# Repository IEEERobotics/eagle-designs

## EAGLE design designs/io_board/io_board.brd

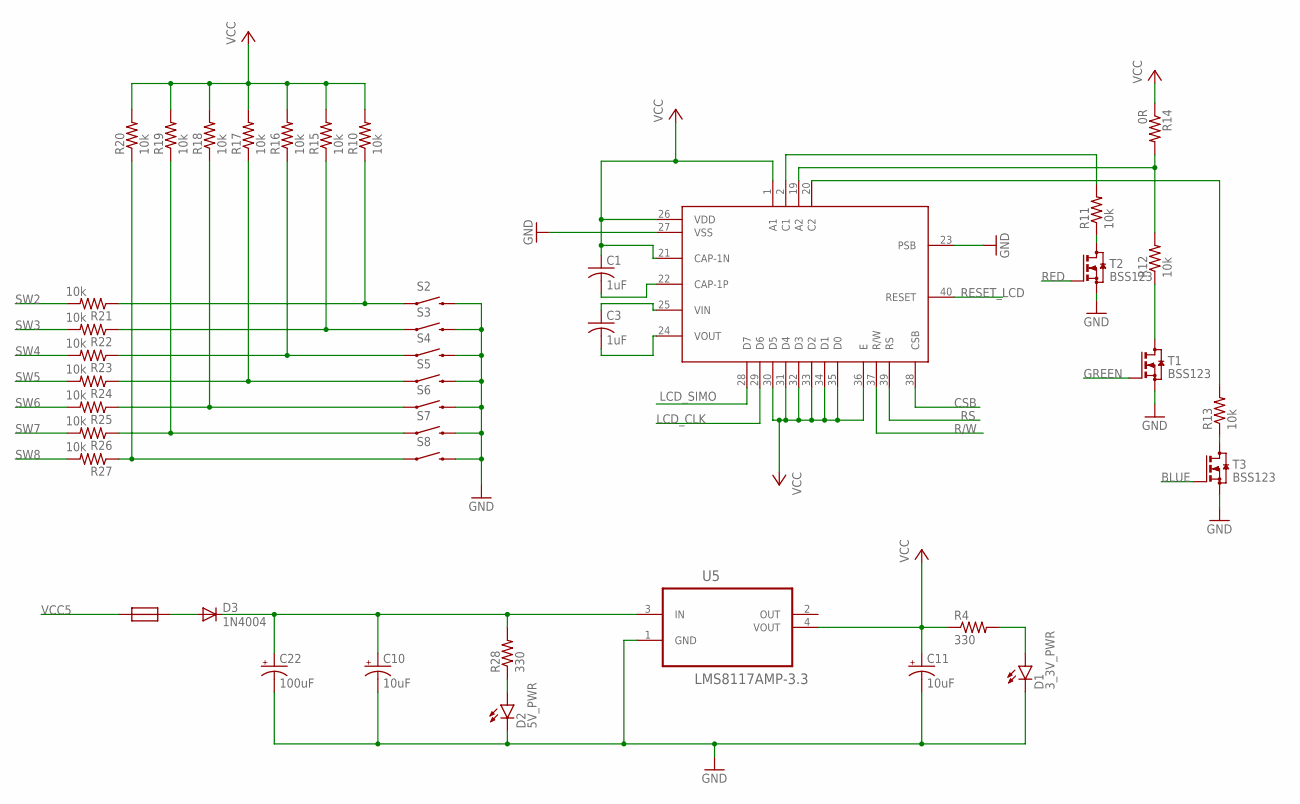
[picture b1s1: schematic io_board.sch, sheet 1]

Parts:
C1, C3: 1uF; C1206K
C10, C11: 10uF; EIA3216
C22: 100uF; EIA7343
D1: 3_3V_PWR; FKIT-LED-1206
D2: 5V_PWR; FKIT-LED-1206
D3: 1N4004; DO41-10
R4, R28: 330; R0805W
R10, R11, R12, R13, R15, R16, R17, R18, R19, R20, R21, R22, R23, R24, R25, R26, R27: 10k; R1206W
R14: 0R; R1206W
S2, S3, S4, S5, S6, S7, S8: SWITCH-MOMENTARY-2SMD-4; TACTILE_SWITCH_TALL
T1, T2, T3: BSS123; SOT23
U5: LMS8117AMP-3.3; SOT230P696X180-4N
U$2: EA_DOGMXXX-A; EADOGM
U$3: NANO_FUSE

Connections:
BLUE: T3.1 (G); also elsewhere on the board
CSB: U$2.38 (CSB); also elsewhere on the board
GND: C10.C (-), C11.C (-), C22.C (-), D1.C, D2.C, S2.B2 (2), S3.B2 (2), S4.B2 (2), S5.B2 (2), S6.B2 (2), S7.B2 (2), S8.B2 (2), T1.2 (S), T2.2 (S), T3.2 (S), U5.1 (GND), U$2.23 (PSB), U$2.27 (VSS); also elsewhere on the board
GREEN: T1.1 (G); also elsewhere on the board
LCD_CLK: U$2.29 (D6); also elsewhere on the board
LCD_SIMO: U$2.28 (D7); also elsewhere on the board
unnamed: R12.2, R14.2, U$2.19 (A2)
unnamed: R11.1, T2.3 (D)
unnamed: R12.1, T1.3 (D)
unnamed: R13.1, T3.3 (D)
unnamed: R11.2, U$2.2 (C1)
unnamed: R13.2, U$2.20 (C2)
unnamed: C1.2, U$2.22 (CAP-1P)
unnamed: C3.1, U$2.25 (VIN)
unnamed: C3.2, U$2.24 (VOUT)
unnamed: R10.1, R21.1, S2.A2 (1)
unnamed: R15.1, R22.1, S3.A2 (1)
unnamed: R16.1, R23.1, S4.A2 (1)
unnamed: R17.1, R24.1, S5.A2 (1)
unnamed: R18.1, R25.1, S6.A2 (1)
unnamed: R19.1, R26.1, S7.A2 (1)
unnamed: R20.1, R27.1, S8.A2 (1)
unnamed: D1.A, R4.2
unnamed: D2.A, R28.1
unnamed: D3.A, U$3.2
unnamed: C10.A (+), C22.A (+), D3.C, R28.2, U5.3 (IN)
R/W: U$2.37 (R/W); also elsewhere on the board
RED: T2.1 (G); also elsewhere on the board
RESET_LCD: U$2.40 (RESET); also elsewhere on the board
RS: U$2.39 (RS)
SW2: R21.2; also elsewhere on the board
SW3: R22.2; also elsewhere on the board
SW4: R23.2; also elsewhere on the board
SW5: R24.2; also elsewhere on the board
SW6: R25.2; also elsewhere on the board
SW7: R26.2; also elsewhere on the board
SW8: R27.2; also elsewhere on the board
VCC: C1.1, C11.A (+), R4.1, R10.2, R14.1, R15.2, R16.2, R17.2, R18.2, R19.2, R20.2, U5.4 (VOUT), U$2.1 (A1), U$2.21 (CAP-1N), U$2.26 (VDD), U$2.30 (D5), U$2.31 (D4), U$2.32 (D3), U$2.33 (D2), U$2.34 (D1), U$2.35 (D0), U$2.36 (E); also elsewhere on the board
VCC5: U$3.1; also elsewhere on the board

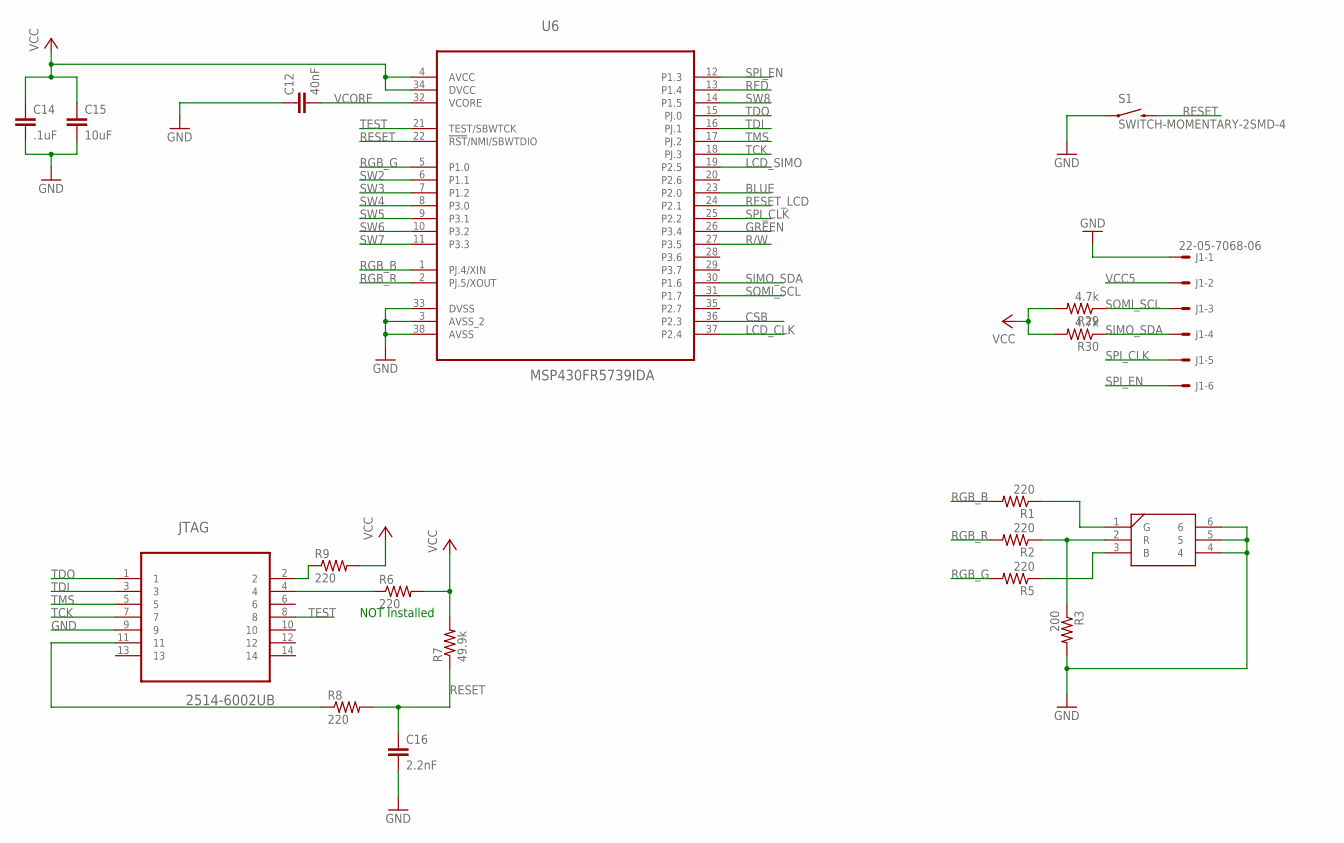
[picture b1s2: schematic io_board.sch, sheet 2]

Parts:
C12: 40nF; 0805
C14: .1uF; 0805
C15: 10uF; 0805
C16: 2.2nF; 0805
J1: 22-05-7068-06; 7395-06
JTAG: 2514-6002UB; 3M_2514-6002UB
R1, R2, R5, R6, R8, R9: 220; R0805W
R3: 200; R0805W
R7: 49.9k; R0805W
R29, R30: 4.7k; R0805W
S1: SWITCH-MOMENTARY-2SMD-4; TACTILE_SWITCH_TALL
U6: MSP430FR5739IDA; SOP65P810X120-38N
U$7: RGB; RGB_SMD

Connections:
BLUE: U6.23 (P2.0); also elsewhere on the board
CSB: U6.36 (P2.3); also elsewhere on the board
GND: C12.1, C14.2, C15.2, C16.2, J1.1, JTAG.9, R3.2, S1.A2 (1), U6.3 (AVSS_2), U6.33 (DVSS), U6.38 (AVSS), U$7.4, U$7.5, U$7.6; also elsewhere on the board
GREEN: U6.26 (P3.4); also elsewhere on the board
LCD_CLK: U6.37 (P2.4); also elsewhere on the board
LCD_SIMO: U6.19 (P2.5); also elsewhere on the board
unnamed: JTAG.4, R6.1
unnamed: JTAG.2, R9.1
unnamed: R2.1, R3.1, U$7.2 (R)
unnamed: JTAG.11, R8.1
unnamed: R5.1, U$7.3 (B)
unnamed: R1.1, U$7.1 (G)
R/W: U6.27 (P3.5); also elsewhere on the board
RED: U6.13 (P1.4); also elsewhere on the board
RESET: C16.1, R7.1, R8.2, S1.B2 (2), U6.22 (!RST!/NMI/SBWTDIO)
RESET_LCD: U6.24 (P2.1); also elsewhere on the board
RGB_B: R1.2, U6.1 (PJ.4/XIN)
RGB_G: R5.2, U6.5 (P1.0)
RGB_R: R2.2, U6.2 (PJ.5/XOUT)
SIMO_SDA: J1.4, R30.1, U6.30 (P1.6)
SOMI_SCL: J1.3, R29.1, U6.31 (P1.7)
SPI_CLK: J1.5, U6.25 (P2.2)
SPI_EN: J1.6, U6.12 (P1.3)
SW2: U6.6 (P1.1); also elsewhere on the board
SW3: U6.7 (P1.2); also elsewhere on the board
SW4: U6.8 (P3.0); also elsewhere on the board
SW5: U6.9 (P3.1); also elsewhere on the board
SW6: U6.10 (P3.2); also elsewhere on the board
SW7: U6.11 (P3.3); also elsewhere on the board
SW8: U6.14 (P1.5); also elsewhere on the board
TCK: JTAG.7, U6.18 (PJ.3)
TDI: JTAG.3, U6.16 (PJ.1)
TDO: JTAG.1, U6.15 (PJ.0)
TEST: JTAG.8, U6.21 (TEST/SBWTCK)
TMS: JTAG.5, U6.17 (PJ.2)
VCC: C14.1, C15.1, R6.2, R7.2, R9.2, R29.2, R30.2, U6.4 (AVCC), U6.34 (DVCC); also elsewhere on the board
VCC5: J1.2; also elsewhere on the board
VCORE: C12.2, U6.32 (VCORE)

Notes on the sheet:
NOT Installed

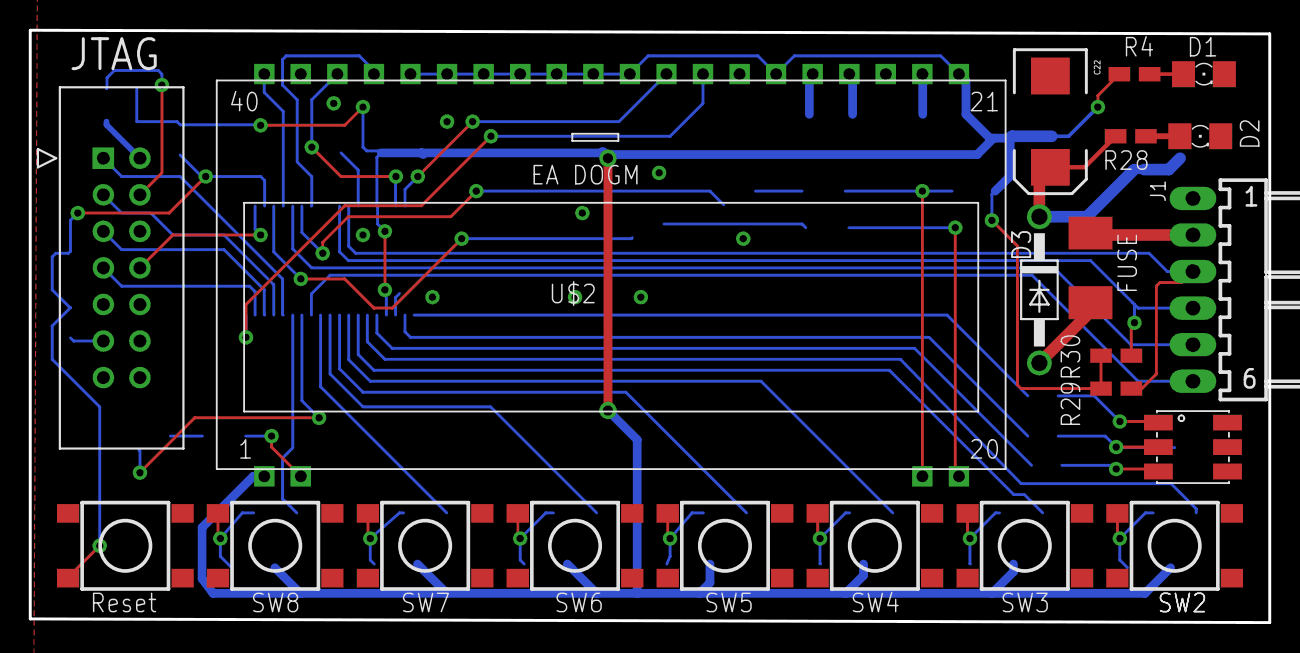
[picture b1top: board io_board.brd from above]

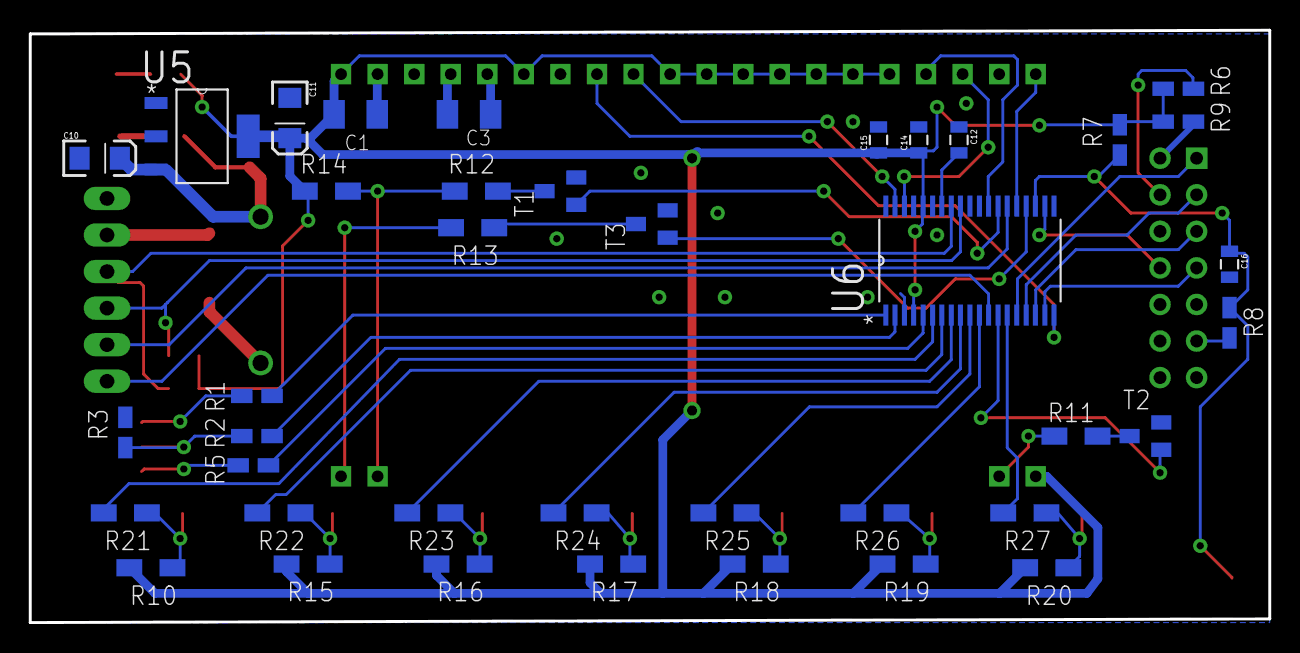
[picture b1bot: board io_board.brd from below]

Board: 2 copper layers, 86.1 x 41.1 mm, 60 parts (39 on the bottom side), 58 nets.

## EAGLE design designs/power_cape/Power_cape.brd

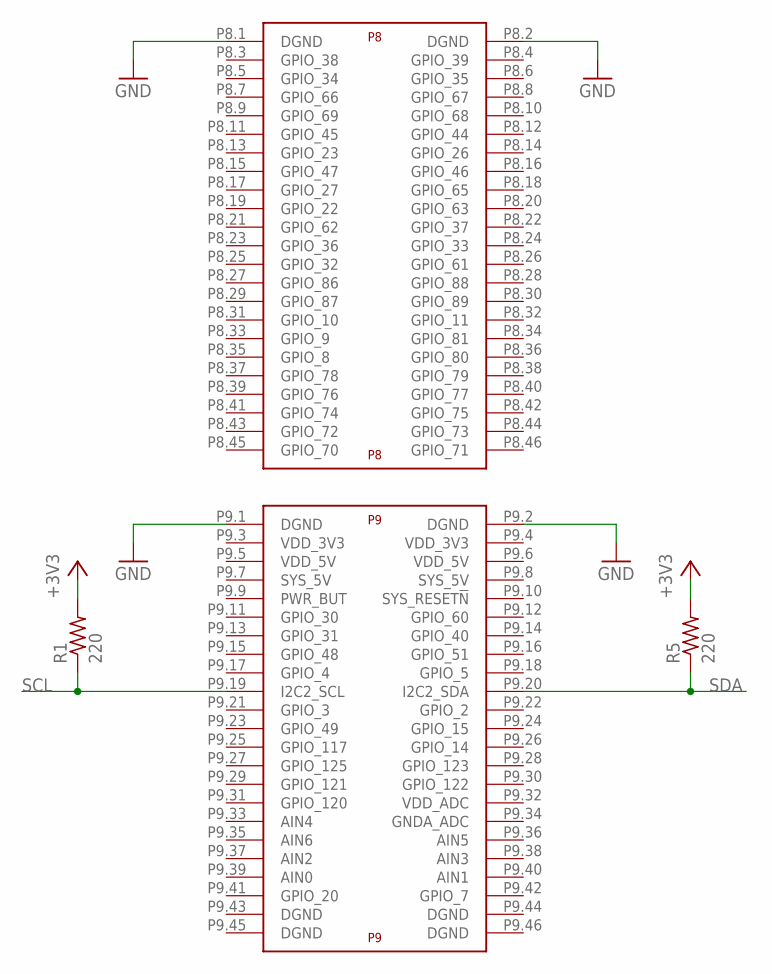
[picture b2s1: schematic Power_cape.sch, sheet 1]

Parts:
R1, R5: 220; R0805W
U$1: BEAGLE_BONE_BLACK_CAPE

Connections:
+3V3: R1.2, R5.2
GND: U$1.P8.1 (DGND), U$1.P8.2 (DGND), U$1.P9.1 (DGND), U$1.P9.2 (DGND); also elsewhere on the board
SCL: R1.1, U$1.P9.19 (I2C2_SCL)
SDA: R5.1, U$1.P9.20 (I2C2_SDA)

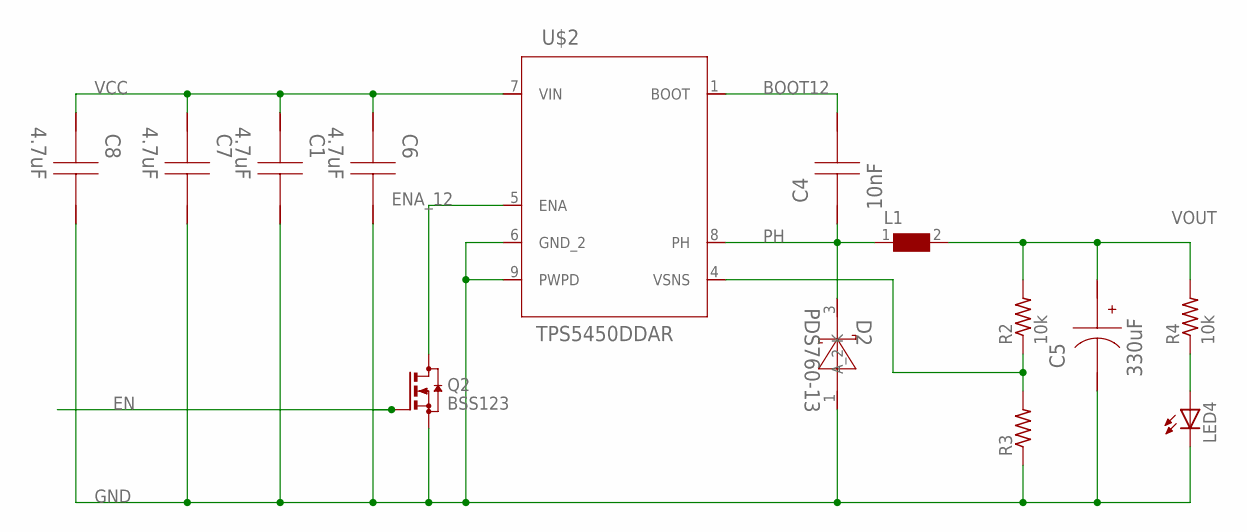
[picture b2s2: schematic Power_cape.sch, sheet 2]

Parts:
C1, C6, C7, C8: 4.7uF; 1206
C4: 10nF; 0805
C5: 330uF; SM_RADIAL_10AMM
D2: PDS760-13; POWERDI5
L1: WE-HCC-7443331000_1090; WE-HCC_1090
LED4: LEDSML1206; SML1206
Q2: BSS123; SOT23
R2, R4: 10k; R1206
R3: R-US_R1206; R1206
U$2: TPS5450DDAR; R-PDSO-G8

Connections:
BOOT12: C4.1, U$2.1 (BOOT)
EN: Q2.1 (G)
ENA_12: Q2.3 (D), U$2.5 (ENA)
GND: C1.1, C5.2 (-), C6.1, C7.1, C8.1, D2.1 (A_2), LED4.C, Q2.2 (S), R3.1, U$2.6 (GND_2), U$2.9 (PWPD); also elsewhere on the board
unnamed: LED4.A, R4.1
PH: C4.2, D2.3 (K), L1.1, U$2.8 (PH)
VCC: C1.2, C6.2, C7.2, C8.2, U$2.7 (VIN)
VOUT: C5.1 (+), L1.2, R2.2, R4.2
VSNS12: R2.1, R3.2, U$2.4 (VSNS)

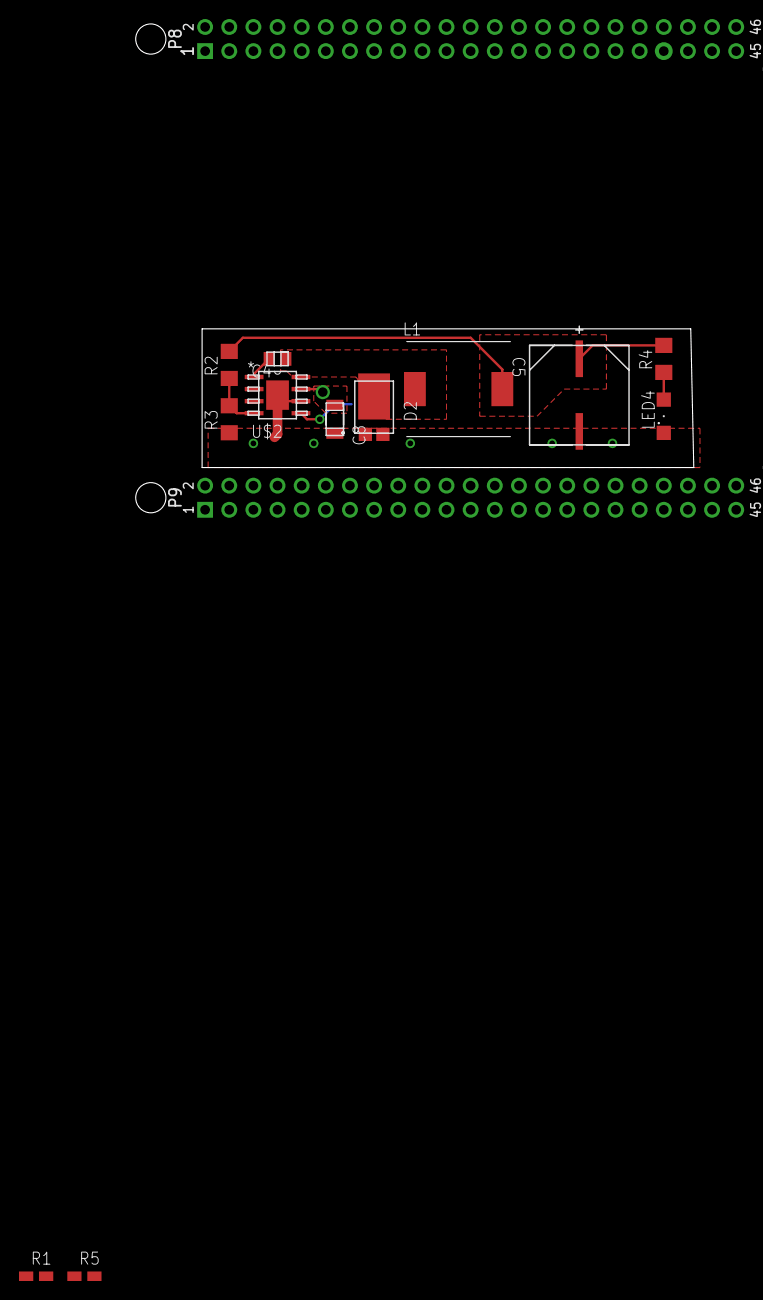
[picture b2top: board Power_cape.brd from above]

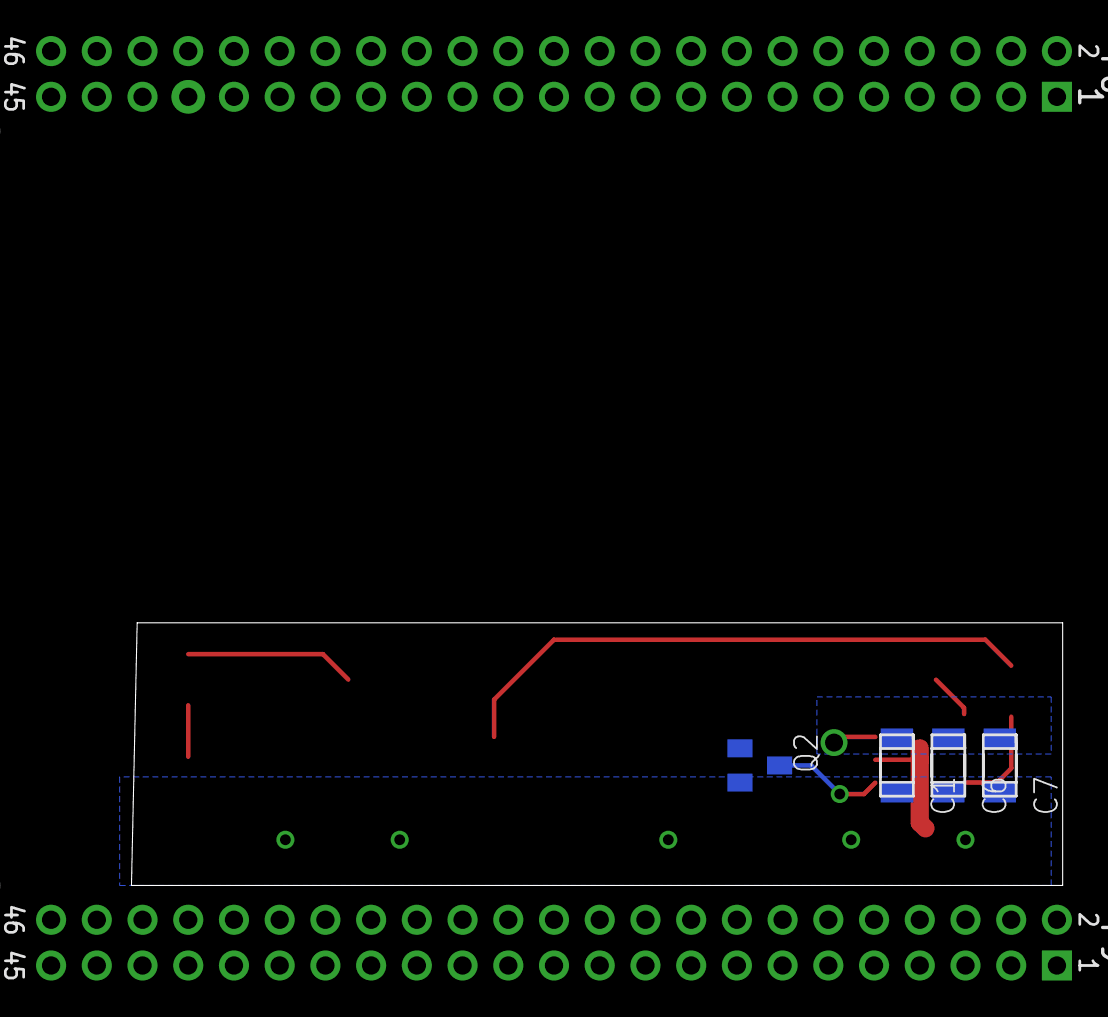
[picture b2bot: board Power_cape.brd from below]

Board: 2 copper layers, 51.7 x 14.6 mm, 17 parts (4 on the bottom side), 11 nets.

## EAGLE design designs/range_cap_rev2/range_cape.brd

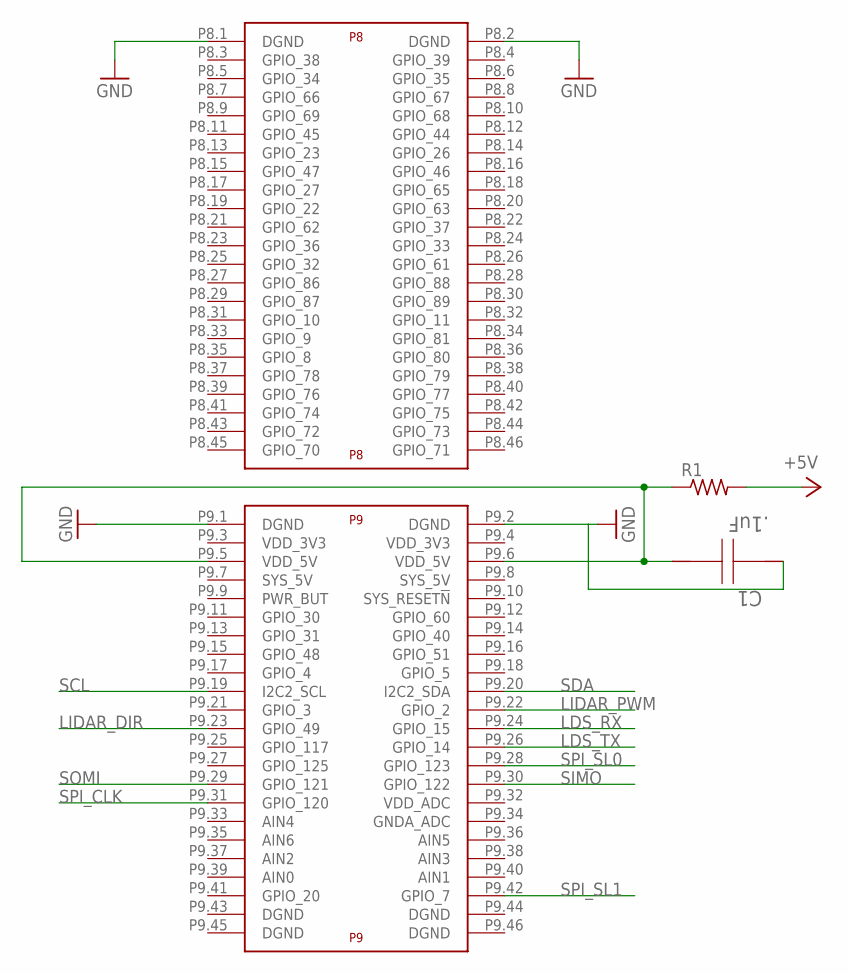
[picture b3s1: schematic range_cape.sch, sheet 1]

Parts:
C1: .1uF; 1206
R1: R-US_R1206; R1206
U$1: BEAGLE_BONE_BLACK_CAPE

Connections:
+5V: R1.2; also elsewhere on the board
GND: C1.2, U$1.P8.1 (DGND), U$1.P8.2 (DGND), U$1.P9.1 (DGND), U$1.P9.2 (DGND); also elsewhere on the board
LDS_RX: U$1.P9.24 (GPIO_15); also elsewhere on the board
LDS_TX: U$1.P9.26 (GPIO_14); also elsewhere on the board
LIDAR_DIR: U$1.P9.23 (GPIO_49); also elsewhere on the board
LIDAR_PWM: U$1.P9.22 (GPIO_2); also elsewhere on the board
unnamed: C1.1, R1.1, U$1.P9.5 (VDD_5V), U$1.P9.6 (VDD_5V)
SCL: U$1.P9.19 (I2C2_SCL); also elsewhere on the board
SDA: U$1.P9.20 (I2C2_SDA); also elsewhere on the board
SIMO: U$1.P9.30 (GPIO_122); also elsewhere on the board
SOMI: U$1.P9.29 (GPIO_121); also elsewhere on the board
SPI_CLK: U$1.P9.31 (GPIO_120); also elsewhere on the board
SPI_SL0: U$1.P9.28 (GPIO_123); also elsewhere on the board
SPI_SL1: U$1.P9.42 (GPIO_7); also elsewhere on the board

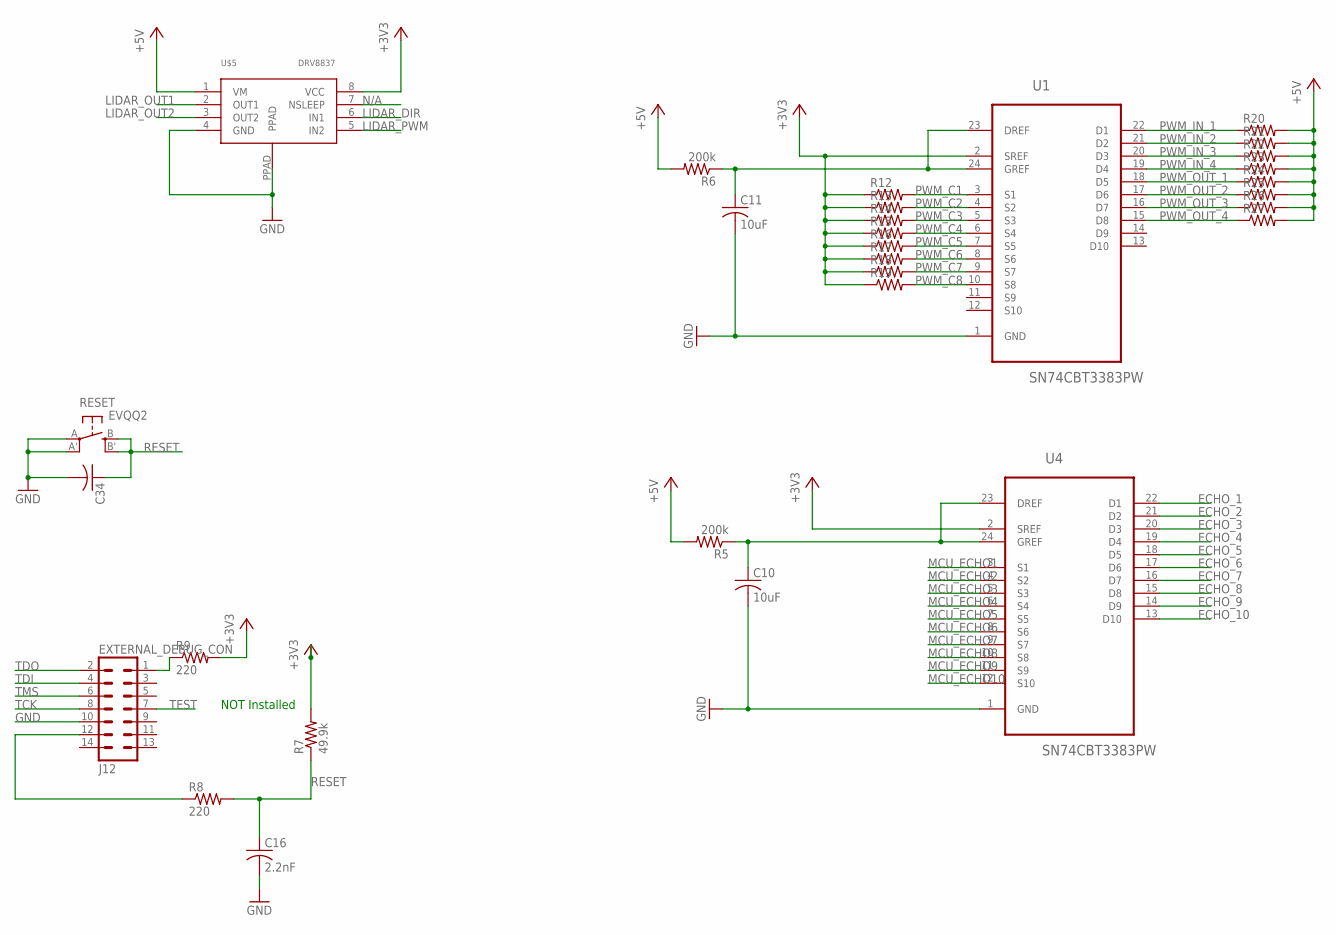
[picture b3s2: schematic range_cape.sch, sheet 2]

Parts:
C10, C11: 10uF; C0805
C16: 2.2nF; C0603
C34: C-USC1206; C1206
J12: EXTERNAL_DEBUG_CON; EXTERNAL_DEBUG
R5, R6: 200k; R0603
R7: 49.9k; R0603
R8, R9: 220; R0603
R12, R13, R14, R15, R16, R17, R18, R19, R20, R21, R22, R23, R24, R25, R26, R27: R-US_R0402; R0402
RESET: EVQQ2; EVQ-Q2
U1, U4: SN74CBT3383PW; SOP65P640X120-24N
U$5: DRV8837; WSON-8

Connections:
+3V3: R7.2, R9.2, R12.1, R13.1, R14.1, R15.1, R16.1, R17.1, R18.1, R19.1, U1.2 (SREF), U4.2 (SREF), U$5.8 (VCC); also elsewhere on the board
+5V: R5.2, R6.2, R20.2, R21.2, R22.2, R23.2, R24.2, R25.2, R26.2, R27.2, U$5.1 (VM); also elsewhere on the board
ECHO_1: U4.22 (D1); also elsewhere on the board
ECHO_2: U4.21 (D2); also elsewhere on the board
ECHO_3: U4.20 (D3); also elsewhere on the board
ECHO_4: U4.19 (D4); also elsewhere on the board
ECHO_5: U4.18 (D5); also elsewhere on the board
ECHO_6: U4.17 (D6); also elsewhere on the board
ECHO_7: U4.16 (D7); also elsewhere on the board
ECHO_8: U4.15 (D8); also elsewhere on the board
ECHO_9: U4.14 (D9); also elsewhere on the board
ECHO_10: U4.13 (D10); also elsewhere on the board
GND: C10.2, C11.2, C16.2, C34.2, J12.10, RESET.A, RESET.A' (P1), U1.1 (GND), U4.1 (GND), U$5.4 (GND), U$5.PPAD; also elsewhere on the board
LIDAR_DIR: U$5.6 (IN1); also elsewhere on the board
LIDAR_OUT1: U$5.2 (OUT1); also elsewhere on the board
LIDAR_OUT2: U$5.3 (OUT2); also elsewhere on the board
LIDAR_PWM: U$5.5 (IN2); also elsewhere on the board
MCU_ECHO1: U4.3 (S1); also elsewhere on the board
MCU_ECHO2: U4.4 (S2); also elsewhere on the board
MCU_ECHO3: U4.5 (S3); also elsewhere on the board
MCU_ECHO4: U4.6 (S4); also elsewhere on the board
MCU_ECHO5: U4.7 (S5); also elsewhere on the board
MCU_ECHO6: U4.8 (S6); also elsewhere on the board
MCU_ECHO7: U4.9 (S7); also elsewhere on the board
MCU_ECHO8: U4.10 (S8); also elsewhere on the board
MCU_ECHO9: U4.11 (S9); also elsewhere on the board
MCU_ECHO10: U4.12 (S10); also elsewhere on the board
unnamed: C11.1, R6.1, U1.23 (DREF), U1.24 (GREF)
unnamed: J12.12, R8.1
unnamed: J12.1, R9.1
unnamed: C10.1, R5.1, U4.23 (DREF), U4.24 (GREF)
N/A: U$5.7 (NSLEEP)
PWM_C1: R12.2, U1.3 (S1); also elsewhere on the board
PWM_C2: R13.2, U1.4 (S2); also elsewhere on the board
PWM_C3: R14.2, U1.5 (S3); also elsewhere on the board
PWM_C4: R15.2, U1.6 (S4); also elsewhere on the board
PWM_C5: R16.2, U1.7 (S5); also elsewhere on the board
PWM_C6: R17.2, U1.8 (S6); also elsewhere on the board
PWM_C7: R18.2, U1.9 (S7); also elsewhere on the board
PWM_C8: R19.2, U1.10 (S8); also elsewhere on the board
PWM_IN_1: R20.1, U1.22 (D1); also elsewhere on the board
PWM_IN_2: R21.1, U1.21 (D2); also elsewhere on the board
PWM_IN_3: R22.1, U1.20 (D3); also elsewhere on the board
PWM_IN_4: R23.1, U1.19 (D4); also elsewhere on the board
PWM_OUT_1: R24.1, U1.18 (D5); also elsewhere on the board
PWM_OUT_2: R25.1, U1.17 (D6); also elsewhere on the board
PWM_OUT_3: R26.1, U1.16 (D7); also elsewhere on the board
PWM_OUT_4: R27.1, U1.15 (D8); also elsewhere on the board
RESET: C16.1, C34.1, R7.1, R8.2, RESET.B (S), RESET.B' (S1); also elsewhere on the board
TCK: J12.8; also elsewhere on the board
TDI: J12.4; also elsewhere on the board
TDO: J12.2; also elsewhere on the board
TEST: J12.7; also elsewhere on the board
TMS: J12.6; also elsewhere on the board

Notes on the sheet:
NOT Installed

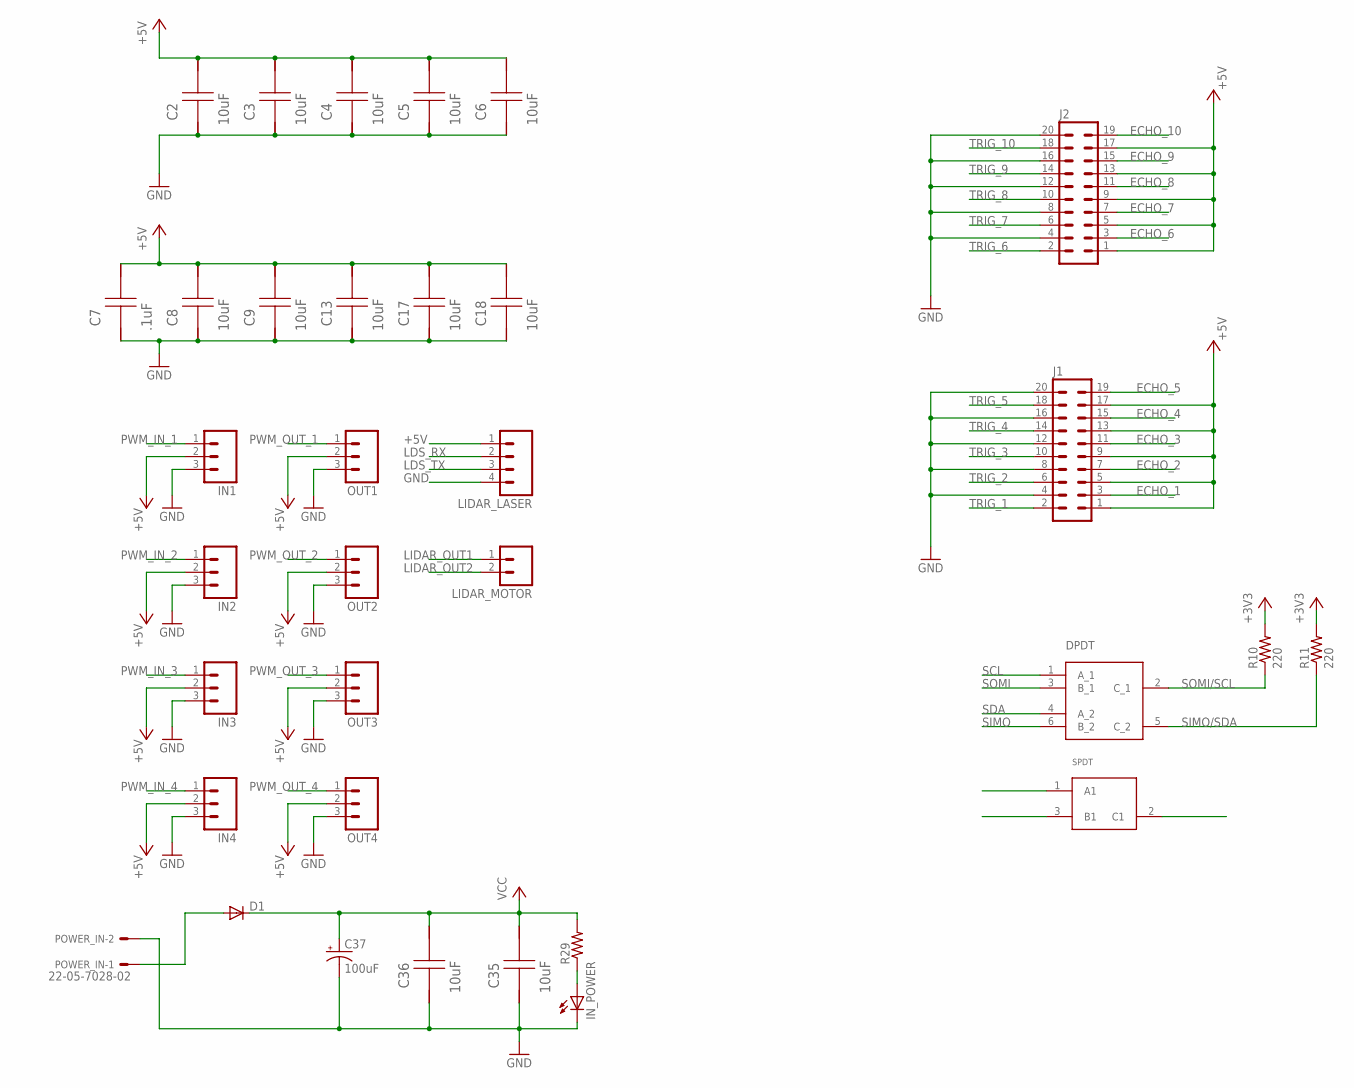
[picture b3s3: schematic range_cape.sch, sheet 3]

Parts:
C2, C3, C4, C5, C6, C8, C9, C13, C17, C18, C35, C36: 10uF; 1206
C7: .1uF; 1206
C37: 100uF; EIA7343
D1: DIODE-DO-214AC; DO-214AC
IN1, IN2, IN3, IN4: M03LOCK; 1X03_LOCK
IN_POWER: LED_ESML0603; LED_SML0603
J1, J2: MA10-2
LIDAR_LASER: M04JST-PTH-VERT; JST-4-PTH-VERT
LIDAR_MOTOR: M02JST-PTH-VERT; JST-2-PTH-VERT
OUT1, OUT2, OUT3, OUT4: M03LOCK; 1X03_LOCK
POWER_IN: 22-05-7028-02; 7395-02
R10, R11: 220; R0402
R29: R-US_R0603; R0603
SPDT: SPDT_SWITCH; SPDT
U$4: DPDT_I2C_SPI; DPDT

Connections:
+3V3: R10.2, R11.2; also elsewhere on the board
+5V: C2.1, C3.1, C4.1, C5.1, C6.1, C7.1, C8.1, C9.1, C13.1, C17.1, C18.1, IN1.2, IN2.2, IN3.2, IN4.2, J1.1, J1.5, J1.9, J1.13, J1.17, J2.1, J2.5, J2.9, J2.13, J2.17, LIDAR_LASER.1, OUT1.2, OUT2.2, OUT3.2, OUT4.2; also elsewhere on the board
ECHO_1: J1.3; also elsewhere on the board
ECHO_2: J1.7; also elsewhere on the board
ECHO_3: J1.11; also elsewhere on the board
ECHO_4: J1.15; also elsewhere on the board
ECHO_5: J1.19; also elsewhere on the board
ECHO_6: J2.3; also elsewhere on the board
ECHO_7: J2.7; also elsewhere on the board
ECHO_8: J2.11; also elsewhere on the board
ECHO_9: J2.15; also elsewhere on the board
ECHO_10: J2.19; also elsewhere on the board
GND: C2.2, C3.2, C4.2, C5.2, C6.2, C7.2, C8.2, C9.2, C13.2, C17.2, C18.2, C35.2, C36.2, C37.C (-), IN1.3, IN2.3, IN3.3, IN4.3, IN_POWER.C, J1.4, J1.8, J1.12, J1.16, J1.20, J2.4, J2.8, J2.12, J2.16, J2.20, LIDAR_LASER.4, OUT1.3, OUT2.3, OUT3.3, OUT4.3, POWER_IN.2; also elsewhere on the board
LDS_RX: LIDAR_LASER.2; also elsewhere on the board
LDS_TX: LIDAR_LASER.3; also elsewhere on the board
LIDAR_OUT1: LIDAR_MOTOR.1; also elsewhere on the board
LIDAR_OUT2: LIDAR_MOTOR.2; also elsewhere on the board
unnamed: D1.A, POWER_IN.1
unnamed: IN_POWER.A, R29.1
PWM_IN_1: IN1.1; also elsewhere on the board
PWM_IN_2: IN2.1; also elsewhere on the board
PWM_IN_3: IN3.1; also elsewhere on the board
PWM_IN_4: IN4.1; also elsewhere on the board
PWM_OUT_1: OUT1.1; also elsewhere on the board
PWM_OUT_2: OUT2.1; also elsewhere on the board
PWM_OUT_3: OUT3.1; also elsewhere on the board
PWM_OUT_4: OUT4.1; also elsewhere on the board
SCL: U$4.1 (A_1); also elsewhere on the board
SDA: U$4.4 (A_2); also elsewhere on the board
SIMO: U$4.6 (B_2); also elsewhere on the board
SIMO/SDA: R11.1, U$4.5 (C_2); also elsewhere on the board
SOMI: U$4.3 (B_1); also elsewhere on the board
SOMI/SCL: R10.1, U$4.2 (C_1); also elsewhere on the board
SPI_SL: SPDT.2 (C1); also elsewhere on the board
SPI_SL0: SPDT.1 (A1); also elsewhere on the board
SPI_SL1: SPDT.3 (B1); also elsewhere on the board
TRIG_1: J1.2; also elsewhere on the board
TRIG_2: J1.6; also elsewhere on the board
TRIG_3: J1.10; also elsewhere on the board
TRIG_4: J1.14; also elsewhere on the board
TRIG_5: J1.18; also elsewhere on the board
TRIG_6: J2.2; also elsewhere on the board
TRIG_7: J2.6; also elsewhere on the board
TRIG_8: J2.10; also elsewhere on the board
TRIG_9: J2.14; also elsewhere on the board
TRIG_10: J2.18; also elsewhere on the board
VCC: C35.1, C36.1, C37.A (+), D1.C, R29.2; also elsewhere on the board

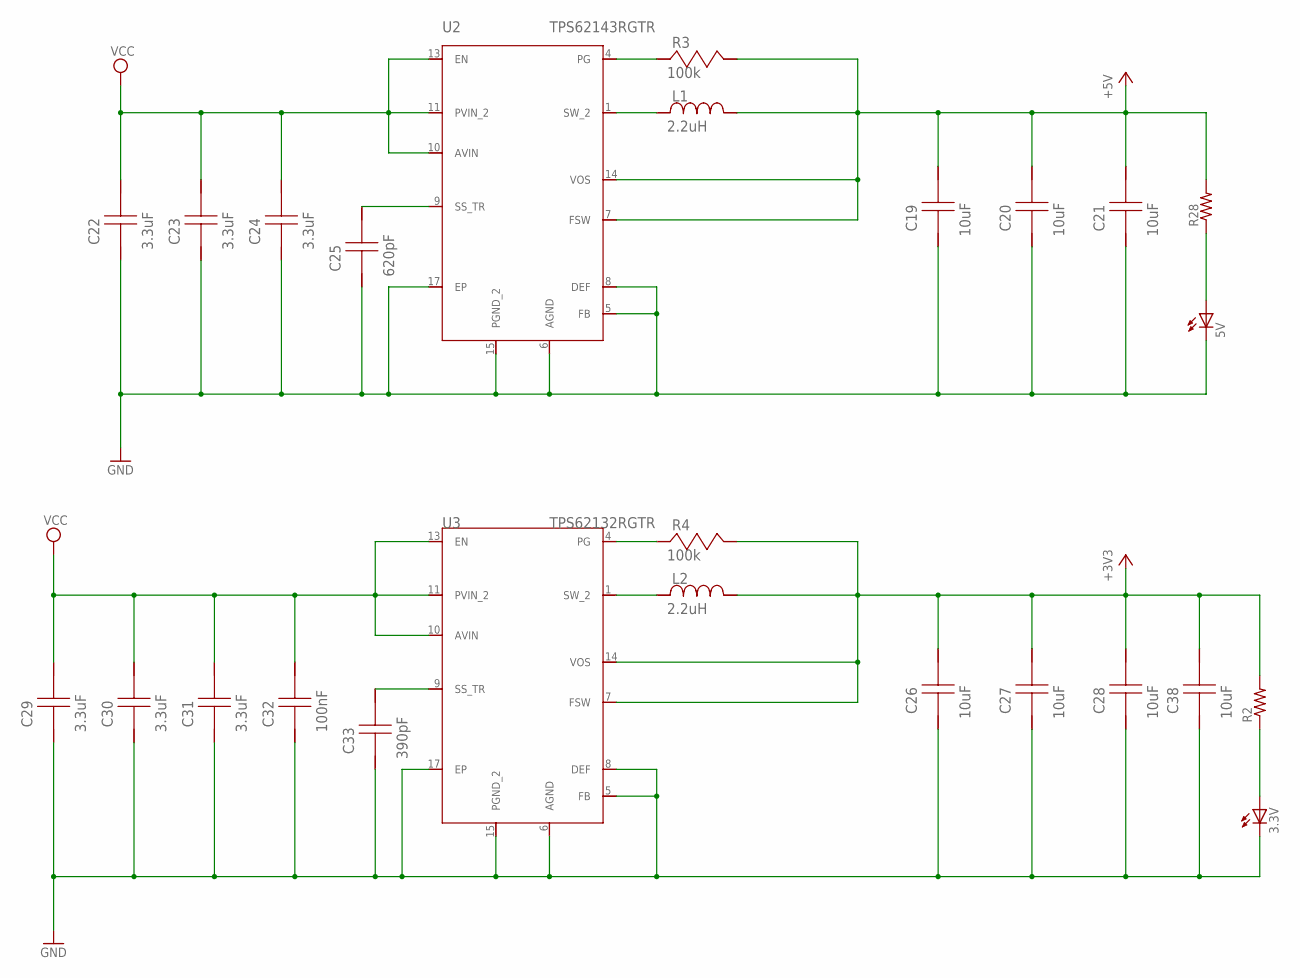
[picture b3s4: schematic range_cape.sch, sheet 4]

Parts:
3.3V, 5V: LED_ESML0603; LED_SML0603
C19, C20, C21, C26, C27, C28, C38: 10uF; 1206
C22, C23, C24, C29, C30, C31: 3.3uF; C3216X7R1E335K
C25: 620pF; 0402
C32: 100nF; 0603
C33: 390pF; 0805
L1, L2: 2.2uH; IHLP-1212BZ
R2, R28: R-US_R0603; R0603
R3, R4: 100k; CRCW0402100KFKED
U2: TPS62143RGTR; S-PVQFN-N16
U3: TPS62132RGTR; S-PVQFN-N16

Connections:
+3V3: C26.1, C27.1, C28.1, C38.1, L2.2, R2.2, R4.1, U3.7 (FSW), U3.14 (VOS); also elsewhere on the board
+5V: C19.1, C20.1, C21.1, L1.2, R3.1, R28.2, U2.7 (FSW), U2.14 (VOS); also elsewhere on the board
GND: 3.3V.C, 5V.C, C19.2, C20.2, C21.2, C22.2, C23.2, C24.2, C25.2, C26.2, C27.2, C28.2, C29.2, C30.2, C31.2, C32.2, C33.2, C38.2, U2.5 (FB), U2.6 (AGND), U2.8 (DEF), U2.15 (PGND_2), U2.17 (EP), U3.5 (FB), U3.6 (AGND), U3.8 (DEF), U3.15 (PGND_2), U3.17 (EP); also elsewhere on the board
unnamed: L2.1, U3.1 (SW_2)
unnamed: L1.1, U2.1 (SW_2)
unnamed: 3.3V.A, R2.1
unnamed: C25.1, U2.9 (SS_TR)
unnamed: 5V.A, R28.1
unnamed: R3.2, U2.4 (PG)
unnamed: R4.2, U3.4 (PG)
unnamed: C33.1, U3.9 (SS_TR)
VCC: C22.1, C23.1, C24.1, C29.1, C30.1, C31.1, C32.1, U2.10 (AVIN), U2.11 (PVIN_2), U2.13 (EN), U3.10 (AVIN), U3.11 (PVIN_2), U3.13 (EN); also elsewhere on the board

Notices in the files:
parts and their libraries:
SparkFun-Capacitors: Licensing: Creative Commons ShareAlike 4.0 International - https://creativecommons.org/licenses/by-sa/4.0
